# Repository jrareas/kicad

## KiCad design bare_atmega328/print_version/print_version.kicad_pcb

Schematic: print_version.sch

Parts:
C1, C2, C4: C; C_Disc_D3.0mm_W1.6mm_P2.50mm
C3, C5: CP; CP_Radial_D5.0mm_P2.00mm
D1: LED; LED_0603_1608Metric
J1, J2, J4: 22-23-2021; PinHeader_1x02_P2.54mm_Vertical; MPN 22-23-2021; Digi-Key_PN WM4200-ND
J3: 640456-3; PinHeader_1x03_P2.54mm_Vertical; MPN 640456-3; Digi-Key_PN A19470-ND
J5, J6: Conn_01x14_Male; PinSocket_1x14_P2.54mm_Vertical
R1: 10k; R_Axial_DIN0204_L3.6mm_D1.6mm_P7.62mm_Horizontal
R2, R3, R4: R; R_Axial_DIN0204_L3.6mm_D1.6mm_P7.62mm_Horizontal
SW1: SW_Push; SW_PUSH_6mm_H7.3mm
U1: ATMEGA328-PU; DIP-28_W7.62mm; MPN ATMEGA328-PU; Digi-Key_PN ATMEGA328-PU-ND
U2: NE555DR; DIP-8_W7.62mm; MPN NE555DR; Digi-Key_PN 296-6501-1-ND
Y1: Crystal; Crystal_HC18-U_Vertical

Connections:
GND: C1.2, C2.1, C3.2, C5.2, D1.2 (A), J2.2, J4.1, J5.8, J6.8, SW1.1, U1.8 (GND), U1.22 (GND), U2.1
unnamed: C1.1, J6.9, U1.9 (PB6), Y1.1
unnamed: C2.2, J6.10, U1.10 (PB7), Y1.2
unnamed: C4.1, J6.1, R1.2, SW1.2, U1.1 (PC6)
unnamed: C4.2, J3.3
unnamed: C5.1, R4.1, U2.2, U2.6
unnamed: D1.1 (K), R2.2
unnamed: J1.2, R2.1
unnamed: J3.1, J6.3, U1.3 (PD1)
unnamed: J3.2, J6.2, U1.2 (PD0)
unnamed: J5.1, U1.15 (PB1)
unnamed: J5.2, U1.16 (PB2)
unnamed: J5.3, U1.17 (PB3)
unnamed: J5.4, U1.18 (PB4)
unnamed: J5.5, U1.19 (PB5)
unnamed: J5.7, U1.21 (AREF)
unnamed: J5.9, U1.23 (PC0)
unnamed: J5.10, U1.24 (PC1)
unnamed: J5.11, U1.25 (PC2)
unnamed: J5.12, U1.26 (PC3)
unnamed: J5.13, U1.27 (PC4)
unnamed: J5.14, U1.28 (PC5)
unnamed: J6.4, U1.4 (PD2), U2.3
unnamed: J6.5, U1.5 (PD3)
unnamed: J6.6, U1.6 (PD4)
unnamed: J6.11, U1.11 (PD5)
unnamed: J6.12, U1.12 (PD6)
unnamed: J6.13, U1.13 (PD7)
unnamed: J6.14, U1.14 (PB0)
unnamed: R3.2, R4.2, U2.7
VCC: C3.1, J1.1, J2.1, J4.2, J5.6, J6.7, R1.1, R3.1, U1.7 (VCC), U1.20 (AVCC), U2.4, U2.8

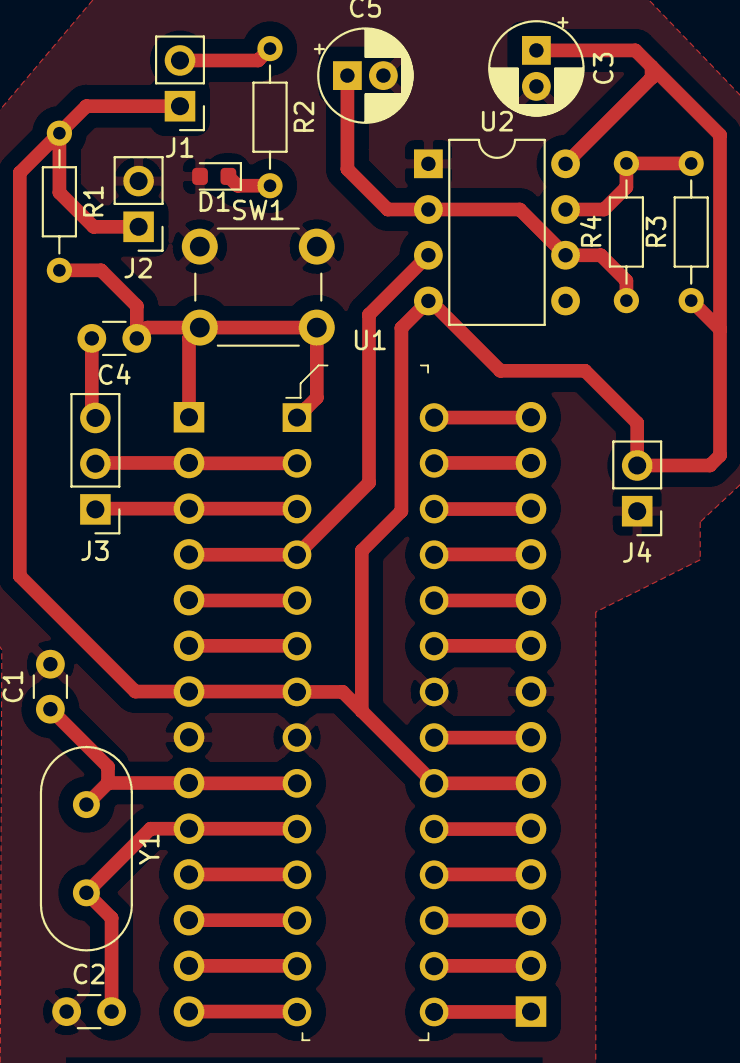
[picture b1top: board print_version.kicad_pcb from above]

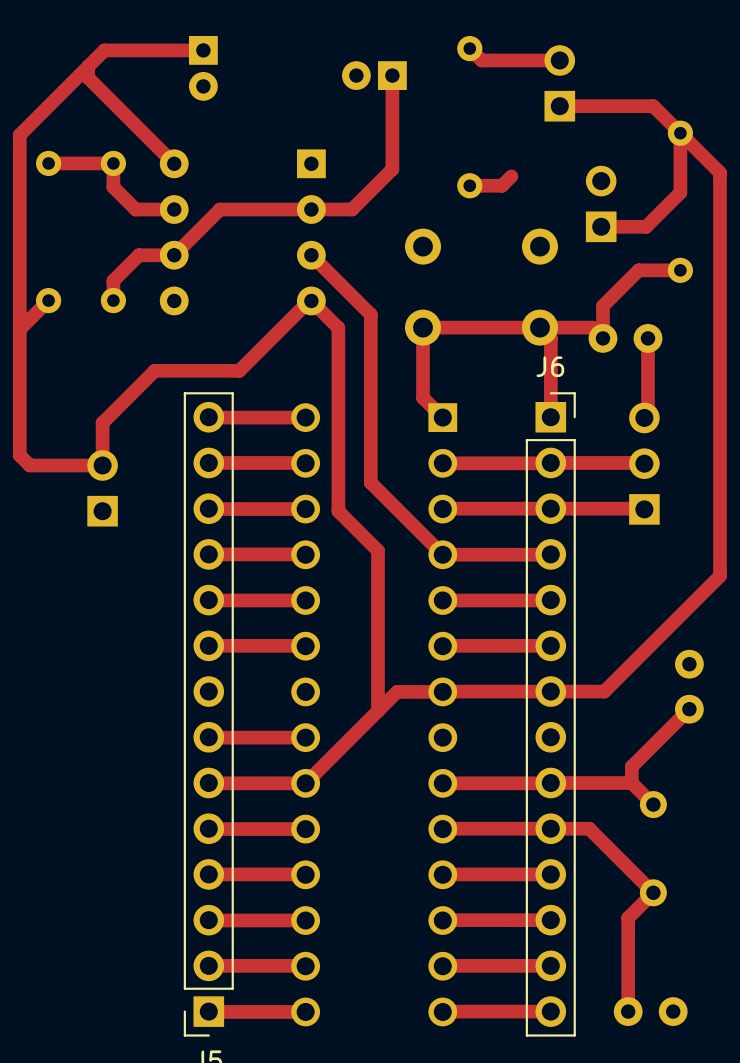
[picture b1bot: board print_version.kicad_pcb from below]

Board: 2 copper layers, 20 parts (2 on the bottom side), 31 nets.

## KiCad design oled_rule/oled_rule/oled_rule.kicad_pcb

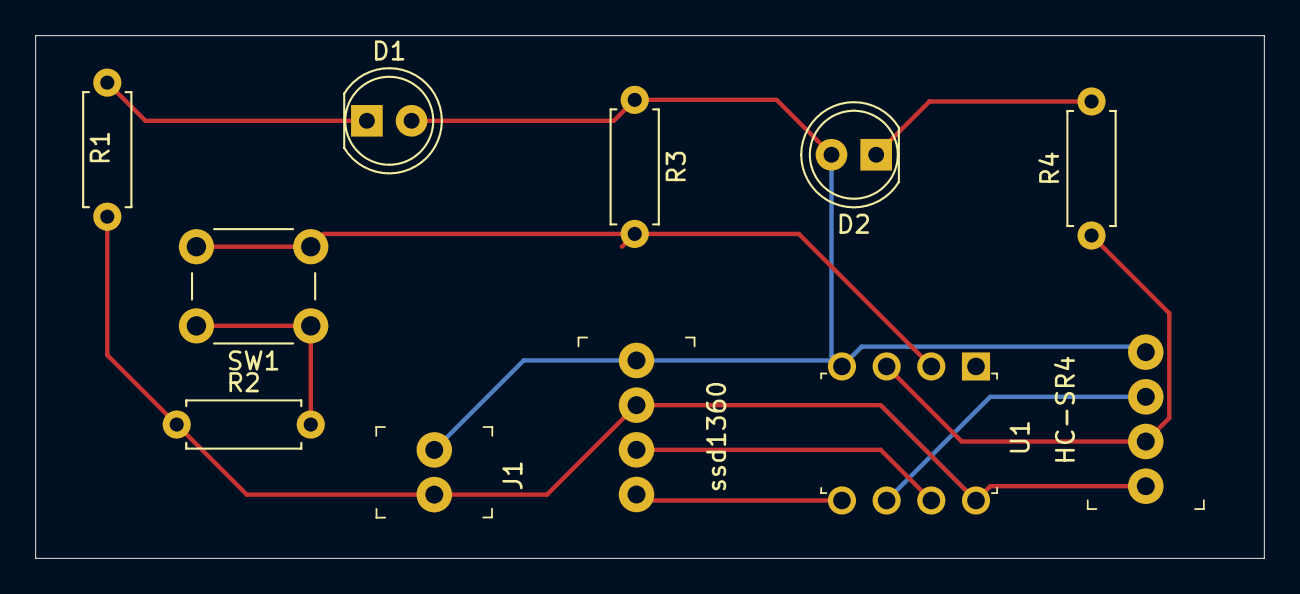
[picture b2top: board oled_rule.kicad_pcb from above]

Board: 2 copper layers, 69.8 x 29.7 mm, 11 parts (0 on the bottom side), 10 nets.

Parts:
D1, D2: LED; LED_D5.0mm
HC-SR4: 0022232041; PinHeader_1x4_P2.54mm_Drill1.02mm
J1: 22-23-2021; PinHeader_1x2_P2.54mm_Drill1.02mm
R1, R2, R3, R4: R; R_Axial_DIN0207_L6.3mm_D2.5mm_P7.62mm_Horizontal
SW1: SW_Push; SW_PUSH_6mm
U1: ATTINY85-20PU; DIP-8_W7.62mm
ssd1360: 0022232041; PinHeader_1x4_P2.54mm_Drill1.02mm

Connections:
GND: D1.2, D2.2, HC-SR4.4, J1.1, U1.4, ssd1360.1
unnamed: D1.1, R1.2
unnamed: D2.1, R4.2
unnamed: HC-SR4.2, R4.1, U1.3
unnamed: HC-SR4.3, U1.6
unnamed: R2.2, SW1.1
unnamed: R3.2, SW1.2, U1.2
unnamed: U1.5, ssd1360.4
unnamed: U1.7, ssd1360.3
VCC: HC-SR4.1, J1.2, R1.1, R2.1, U1.8, ssd1360.2

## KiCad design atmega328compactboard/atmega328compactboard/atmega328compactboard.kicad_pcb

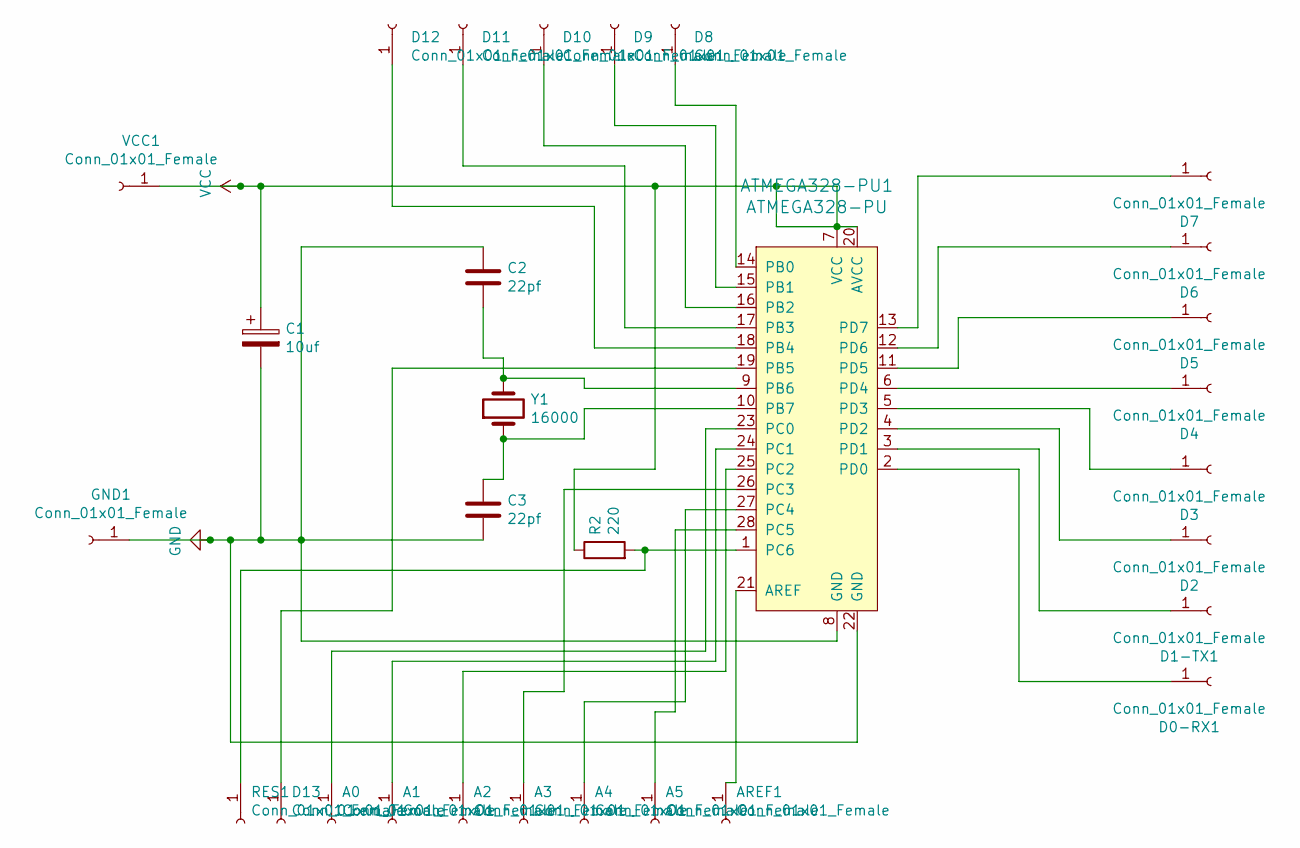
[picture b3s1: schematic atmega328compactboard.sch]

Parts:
A0, A1, A2, A3, A4, A5: Conn_01x01_Female; Pin_D0.7mm_L6.5mm_W1.8mm_FlatFork
AREF1: Conn_01x01_Female; Pin_D0.7mm_L6.5mm_W1.8mm_FlatFork
ATMEGA328-PU1: ATMEGA328-PU; DIP-28_W7.62mm; MPN ATMEGA328-PU; Digi-Key_PN ATMEGA328-PU-ND
C1: 10uf; CP_Radial_Tantal_D5.0mm_P2.50mm
C2, C3: 22pf; C_Disc_D3.0mm_W1.6mm_P2.50mm
D0-RX1, D1-TX1, D2, D3, D4, D5, D6, D7, D8, D9, D10, D11, D12, D13: Conn_01x01_Female; Pin_D0.7mm_L6.5mm_W1.8mm_FlatFork
GND1: Conn_01x01_Female; Pin_D0.7mm_L6.5mm_W1.8mm_FlatFork
R2: 220; R_Axial_DIN0207_L6.3mm_D2.5mm_P7.62mm_Horizontal
RES1: Conn_01x01_Female; Pin_D0.7mm_L6.5mm_W1.8mm_FlatFork
VCC1: Conn_01x01_Female; Pin_D0.7mm_L6.5mm_W1.8mm_FlatFork
Y1: 16000; Resonator-2Pin_W10.0mm_H5.0mm

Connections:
GND: ATMEGA328-PU1.8 (GND), ATMEGA328-PU1.22 (GND), C1.2, C2.1, C3.2, GND1.1
unnamed: A0.1, ATMEGA328-PU1.23 (PC0)
unnamed: A1.1, ATMEGA328-PU1.24 (PC1)
unnamed: A2.1, ATMEGA328-PU1.25 (PC2)
unnamed: A3.1, ATMEGA328-PU1.26 (PC3)
unnamed: A4.1, ATMEGA328-PU1.27 (PC4)
unnamed: A5.1, ATMEGA328-PU1.28 (PC5)
unnamed: AREF1.1, ATMEGA328-PU1.21 (AREF)
unnamed: ATMEGA328-PU1.1 (PC6), R2.2, RES1.1
unnamed: ATMEGA328-PU1.2 (PD0), D0-RX1.1
unnamed: ATMEGA328-PU1.3 (PD1), D1-TX1.1
unnamed: ATMEGA328-PU1.4 (PD2), D2.1
unnamed: ATMEGA328-PU1.5 (PD3), D3.1
unnamed: ATMEGA328-PU1.6 (PD4), D4.1
unnamed: ATMEGA328-PU1.9 (PB6), C2.2, Y1.2
unnamed: ATMEGA328-PU1.10 (PB7), C3.1, Y1.1
unnamed: ATMEGA328-PU1.11 (PD5), D5.1
unnamed: ATMEGA328-PU1.12 (PD6), D6.1
unnamed: ATMEGA328-PU1.13 (PD7), D7.1
unnamed: ATMEGA328-PU1.14 (PB0), D8.1
unnamed: ATMEGA328-PU1.15 (PB1), D9.1
unnamed: ATMEGA328-PU1.16 (PB2), D10.1
unnamed: ATMEGA328-PU1.17 (PB3), D11.1
unnamed: ATMEGA328-PU1.18 (PB4), D12.1
unnamed: ATMEGA328-PU1.19 (PB5), D13.1
VCC: ATMEGA328-PU1.7 (VCC), ATMEGA328-PU1.20 (AVCC), C1.1, R2.1, VCC1.1

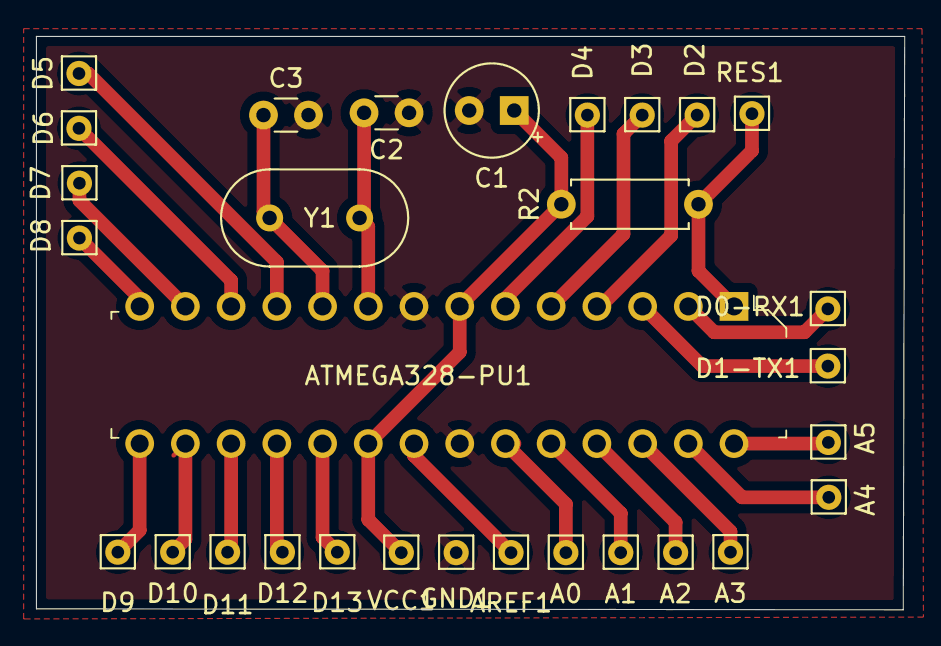
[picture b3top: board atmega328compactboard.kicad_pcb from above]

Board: 2 copper layers, 48.2 x 31.9 mm, 30 parts (0 on the bottom side), 26 nets.

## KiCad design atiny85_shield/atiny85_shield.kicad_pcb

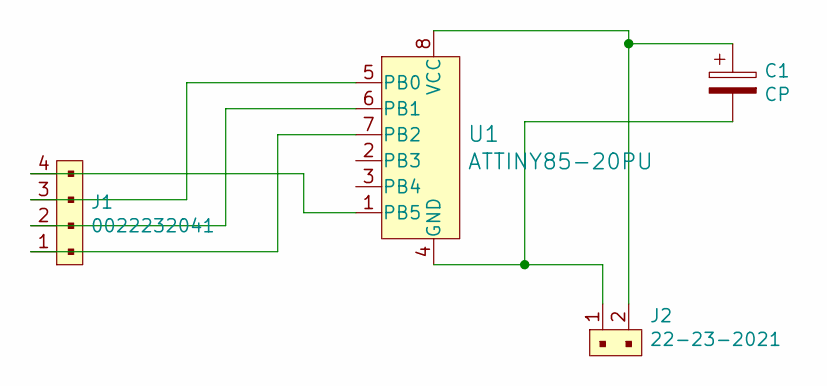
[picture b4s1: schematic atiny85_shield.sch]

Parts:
C1: CP; CP_Radial_D5.0mm_P2.50mm
J1: 0022232041; PinHeader_1x4_P2.54mm_Drill1.02mm; MPN 0022232041; Digi-Key_PN WM4202-ND
J2: 22-23-2021; PinHeader_1x2_P2.54mm_Drill1.02mm; MPN 22-23-2021; Digi-Key_PN WM4200-ND
U1: ATTINY85-20PU; DIP-8_W7.62mm; MPN ATTINY85-20PU; Digi-Key_PN ATTINY85-20PU-ND

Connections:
unnamed: C1.1, J2.2, U1.8 (VCC)
unnamed: C1.2, J2.1, U1.4 (GND)
unnamed: J1.1, U1.7 (PB2)
unnamed: J1.2, U1.6 (PB1)
unnamed: J1.3, U1.5 (PB0)
unnamed: J1.4, U1.1 (PB5)

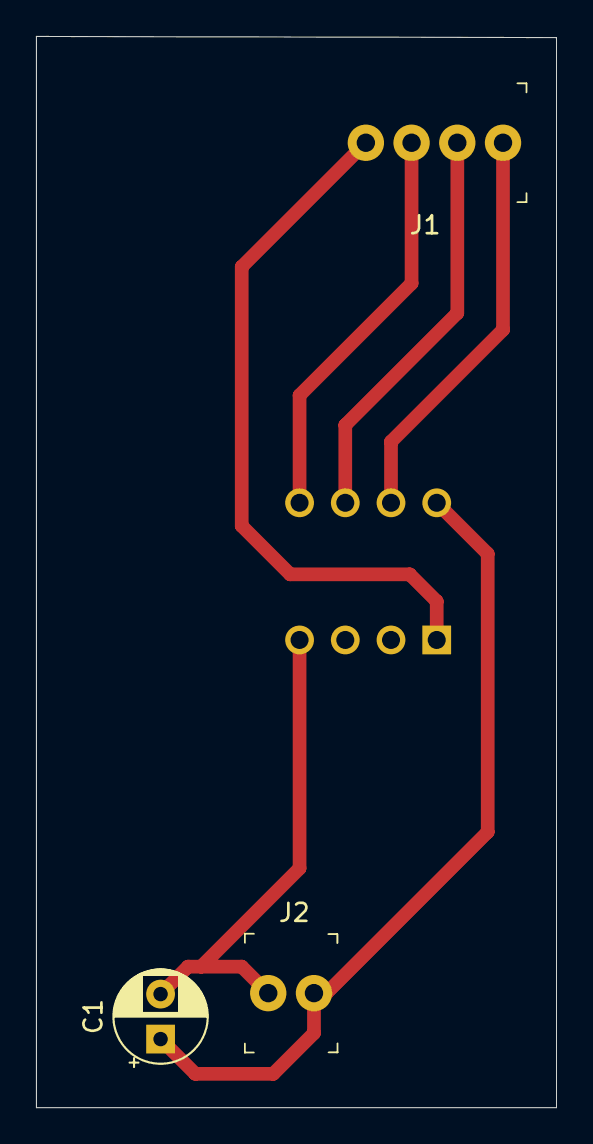
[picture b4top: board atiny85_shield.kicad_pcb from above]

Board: 2 copper layers, 28.9 x 59.5 mm, 4 parts (1 on the bottom side), 6 nets.

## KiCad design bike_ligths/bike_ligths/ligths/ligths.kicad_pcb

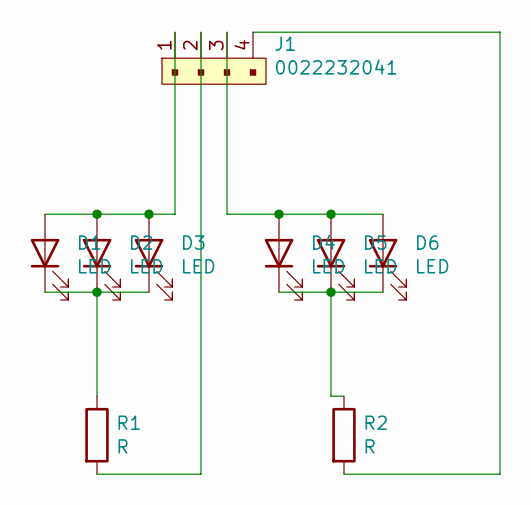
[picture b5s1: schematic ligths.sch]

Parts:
D1, D2, D3, D4, D5, D6: LED; LED_D5.0mm
J1: 0022232041; PinHeader_1x4_P2.54mm_Drill1.02mm; MPN 0022232041; Digi-Key_PN WM4202-ND
R1, R2: R; R_Axial_DIN0204_L3.6mm_D1.6mm_P7.62mm_Horizontal

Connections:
unnamed: D1.1 (K), D2.1 (K), D3.1 (K), R1.1
unnamed: D1.2 (A), D2.2 (A), D3.2 (A), J1.1
unnamed: D4.1 (K), D5.1 (K), D6.1 (K), R2.1
unnamed: D4.2 (A), D5.2 (A), D6.2 (A), J1.3
unnamed: J1.2, R1.2
unnamed: J1.4, R2.2

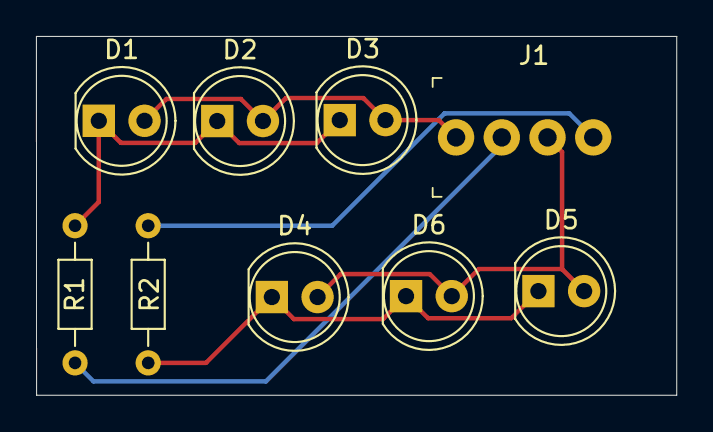
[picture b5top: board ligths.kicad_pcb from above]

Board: 2 copper layers, 35.6 x 19.9 mm, 9 parts (0 on the bottom side), 6 nets.

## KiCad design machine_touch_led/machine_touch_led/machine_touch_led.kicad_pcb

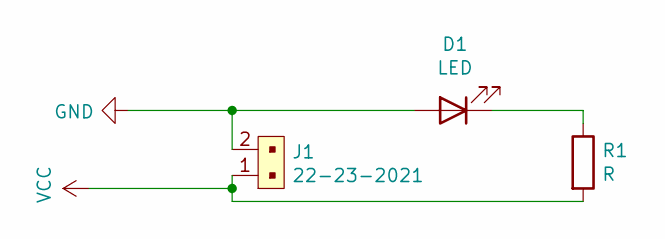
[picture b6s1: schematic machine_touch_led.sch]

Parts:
D1: LED; LED_D5.0mm_Clear
J1: 22-23-2021; PinHeader_1x2_P2.54mm_Drill1.02mm; MPN 22-23-2021; Digi-Key_PN WM4200-ND
R1: R; R_Axial_DIN0411_L9.9mm_D3.6mm_P7.62mm_Vertical

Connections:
GND: D1.2 (A), J1.2
unnamed: D1.1 (K), R1.1
VCC: J1.1, R1.2

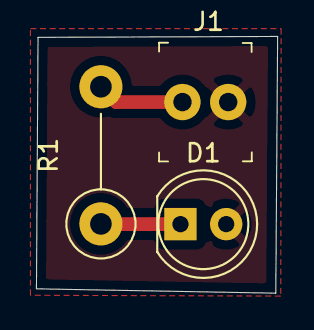
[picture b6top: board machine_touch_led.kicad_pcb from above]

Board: 2 copper layers, 13.4 x 14.3 mm, 3 parts (0 on the bottom side), 3 nets.

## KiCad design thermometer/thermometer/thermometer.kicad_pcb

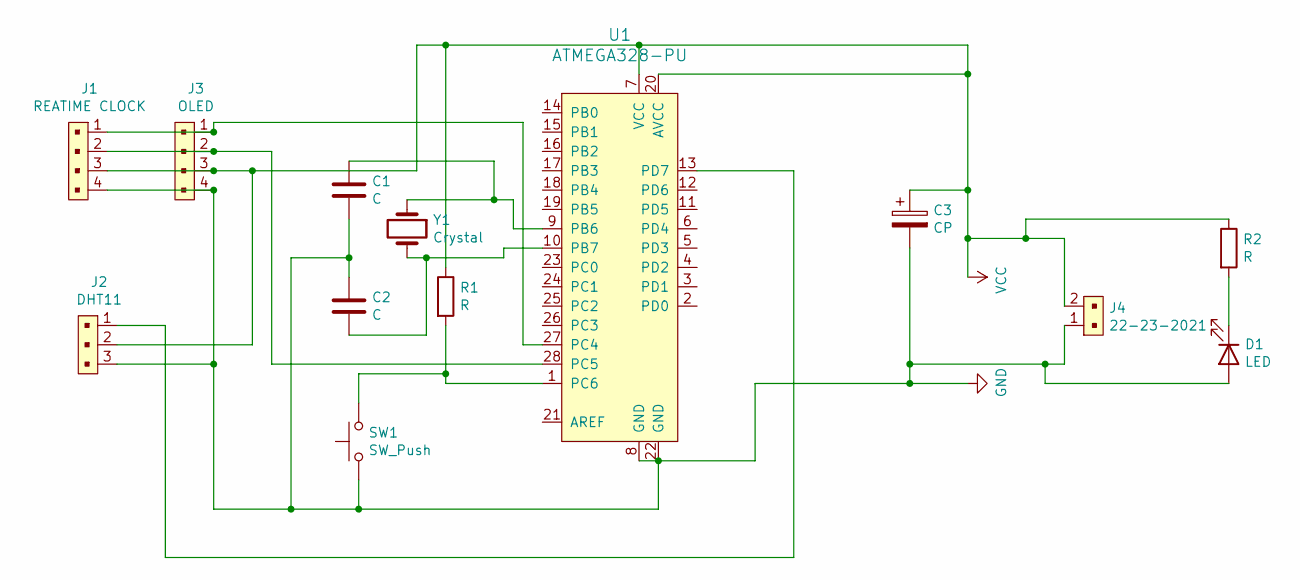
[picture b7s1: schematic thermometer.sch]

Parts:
C1, C2: C; C_Disc_D3.0mm_W1.6mm_P2.50mm
C3: CP; CP_Radial_D5.0mm_P2.00mm
D1: LED; LED_1210_3225Metric_Pad1.42x2.65mm_HandSolder
J1: REATIME CLOCK; PinHeader_1x4_P2.54mm_Drill1.02mm; MPN 0022232041; Digi-Key_PN WM4202-ND
J2: DHT11; PinHeader_1x3_P2.54_Drill1.1mm; MPN 640456-3; Digi-Key_PN A19470-ND
J3: OLED; PinHeader_1x4_P2.54mm_Drill1.02mm; MPN 0022232041; Digi-Key_PN WM4202-ND
J4: 22-23-2021; PinHeader_1x2_P2.54mm_Drill1.02mm; MPN 22-23-2021; Digi-Key_PN WM4200-ND
R1, R2: R; R_Axial_DIN0204_L3.6mm_D1.6mm_P7.62mm_Horizontal
SW1: SW_Push; SW_PUSH_6mm_H7.3mm
U1: ATMEGA328-PU; DIP-28_W7.62mm; MPN ATMEGA328-PU; Digi-Key_PN ATMEGA328-PU-ND
Y1: Crystal; Crystal_HC18-U_Vertical

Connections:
GND: C1.2, C2.1, C3.2, D1.2 (A), J1.4, J2.3, J3.4, J4.1, SW1.1, U1.8 (GND), U1.22 (GND)
unnamed: C1.1, U1.9 (PB6), Y1.1
unnamed: C2.2, U1.10 (PB7), Y1.2
unnamed: D1.1 (K), R2.2
unnamed: J1.1, J3.1, U1.27 (PC4)
unnamed: J1.2, J3.2, U1.28 (PC5)
unnamed: J2.1, U1.13 (PD7)
unnamed: R1.2, SW1.2, U1.1 (PC6)
VCC: C3.1, J1.3, J2.2, J3.3, J4.2, R1.1, R2.1, U1.7 (VCC), U1.20 (AVCC)

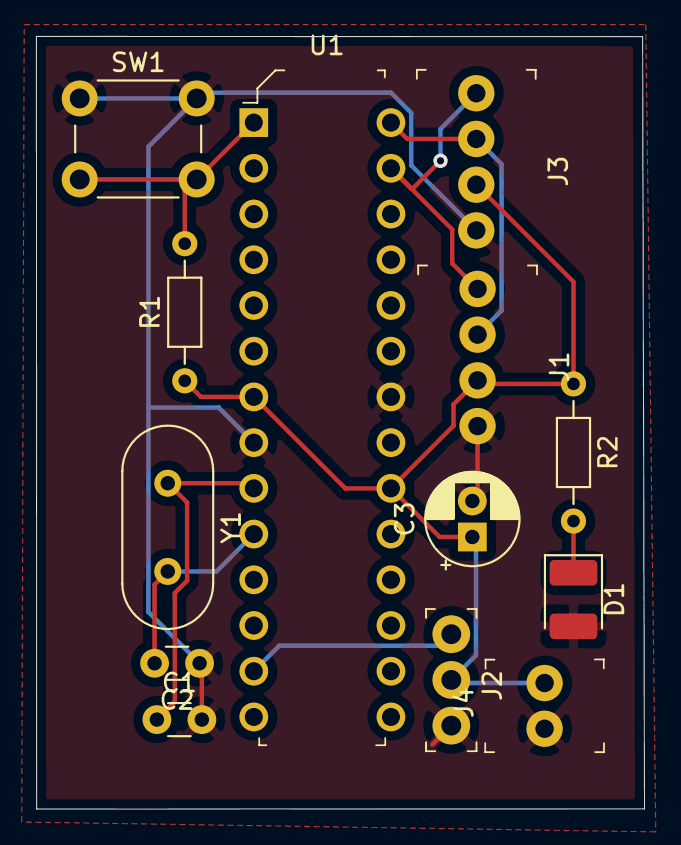
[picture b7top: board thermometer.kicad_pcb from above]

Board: 2 copper layers, 33.8 x 42.9 mm, 13 parts (0 on the bottom side), 9 nets.

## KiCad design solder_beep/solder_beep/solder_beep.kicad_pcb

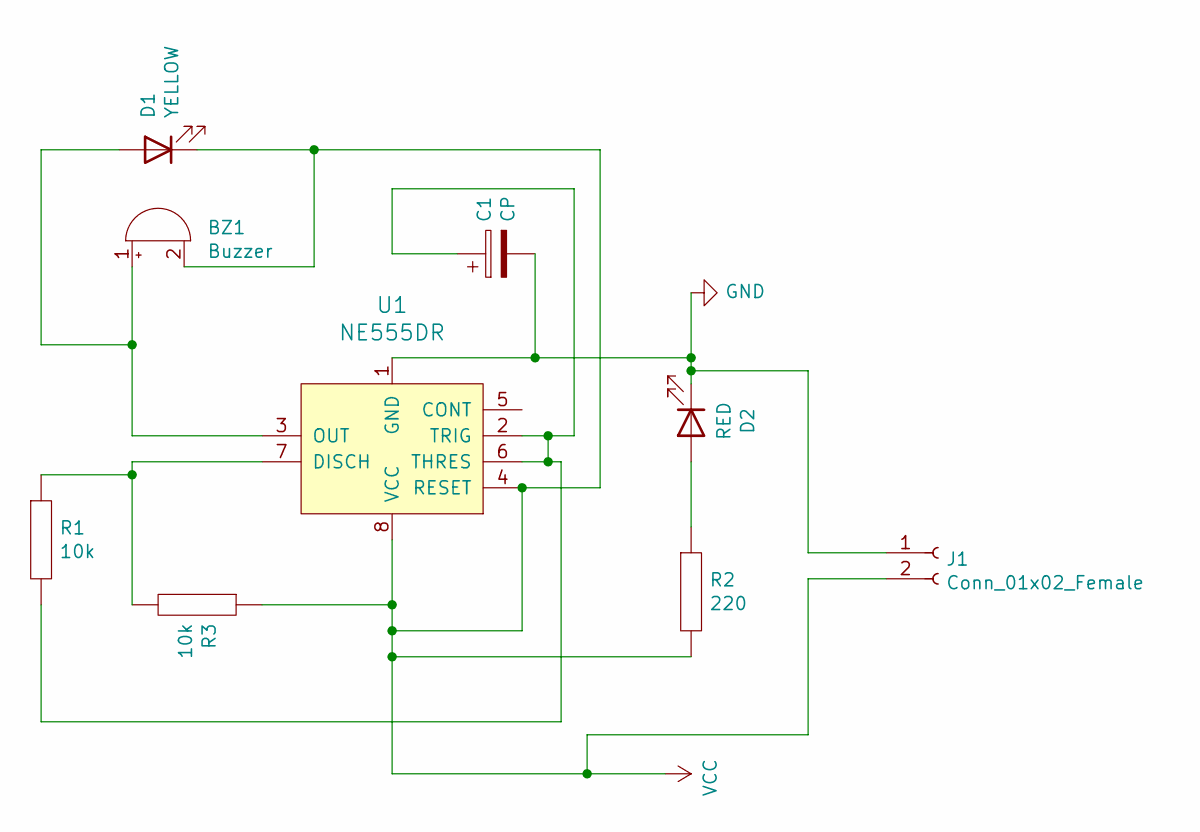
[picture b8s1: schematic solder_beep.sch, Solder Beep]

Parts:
BZ1: Buzzer; Buzzer_12x9.5RM7.6
C1: CP; C_Disc_D3.0mm_W1.6mm_P2.50mm
D1: YELLOW; LED_0603_1608Metric
D2: RED; LED_0603_1608Metric
J1: Conn_01x02_Female; PinHeader_1x02_P2.54mm_Vertical
R1, R3: 10k; R_Axial_DIN0411_L9.9mm_D3.6mm_P7.62mm_Vertical
R2: 220; R_Axial_DIN0411_L9.9mm_D3.6mm_P7.62mm_Vertical
U1: NE555DR; SOIC-8_3.9x4.9mm_P1.27mm; MPN NE555DR; Digi-Key_PN 296-6501-1-ND

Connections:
GND: C1.2, D2.1 (K), J1.1, U1.1 (GND)
unnamed: BZ1.1 (-), D1.2 (A), U1.3 (OUT)
unnamed: C1.1, R1.2, U1.2 (TRIG), U1.6 (THRES)
unnamed: D2.2 (A), R2.1
unnamed: R1.1, R3.2, U1.7 (DISCH)
VCC: BZ1.2 (+), D1.1 (K), J1.2, R2.2, R3.1, U1.4 (RESET), U1.8 (VCC)

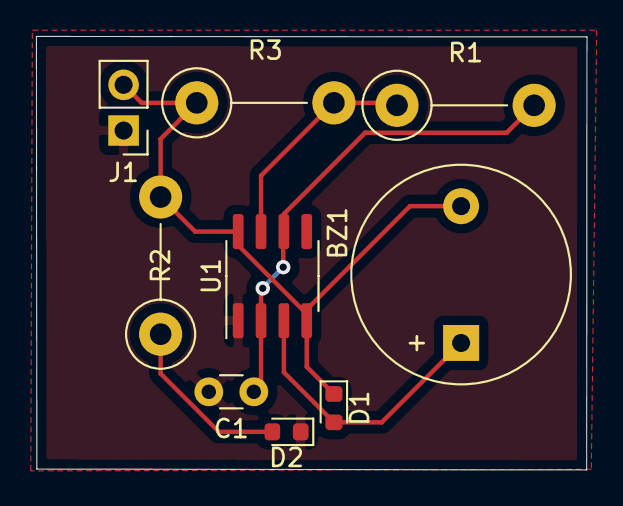
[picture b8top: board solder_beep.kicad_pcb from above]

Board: 2 copper layers, 30.6 x 24.1 mm, 9 parts (0 on the bottom side), 6 nets.

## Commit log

2020-09-25 Bare atmega w/o 555
2020-09-25 Version with 555 dip
2020-09-30 Version v1.2 atmega328 + 555 timer
